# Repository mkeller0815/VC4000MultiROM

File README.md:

VC4000 MultiRom Modul
=====================

This is the approach to implement a MultiRom modul for the Interton VC4000.

![Overview] (https://github.com/mkeller0815/VC4000MultiROM/blob/master/doc/multirom_overview.jpg)

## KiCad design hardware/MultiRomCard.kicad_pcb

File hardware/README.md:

Hardware files for the MultiRom Cartridge
=========================================

You need [KiCad](http://kicad-pcb.org) 4.0 or later to open the project files.

The file MultiRomCard-cache.lib is included here for convenience. If you have
the KiCad standard symbol libraries installed, you do not need this file.
Currently, the only items from the standard libraries are the schematic symbols
for the 74HC595 Shift Register and the 74HC245 Bus Transciever. All other
schematic symbols are custom made and included in MultiRomCard.lib.

The Printouts folder contains PDF plots of the schematic and of the two current
PCB copper layers.  They can be used to create a double sided PCB with DIY
methods like toner transfer.

![Schematic] (https://rawgithub.com/mkeller0815/VC4000MultiROM/master/hardware/MultiRomCard.svg)

![PCB] (https://rawgithub.com/mkeller0815/VC4000MultiROM/master/hardware/MultiRomCard-brd.svg)

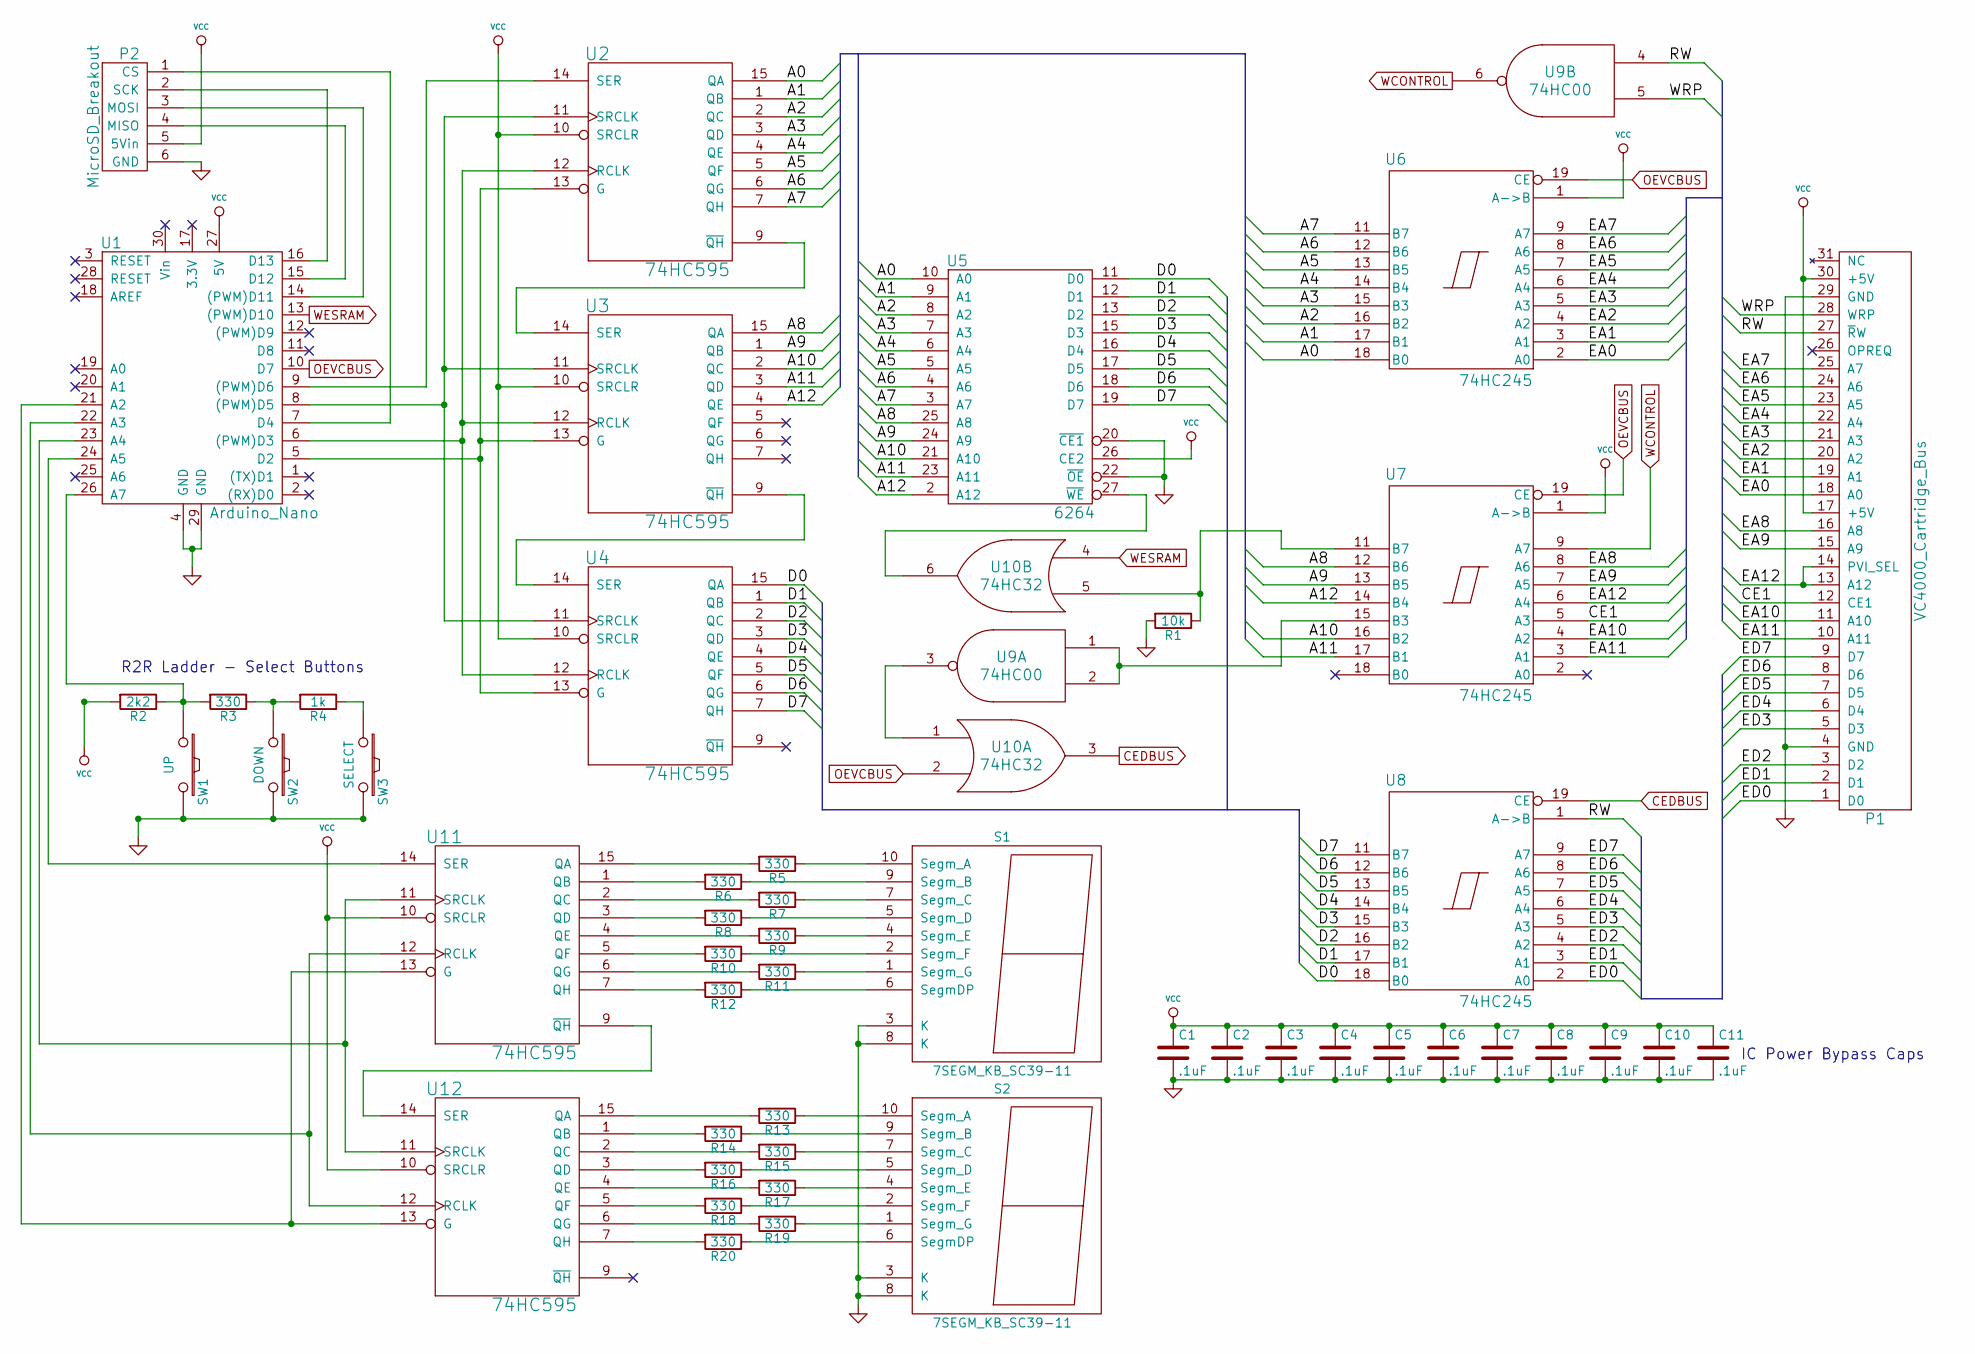
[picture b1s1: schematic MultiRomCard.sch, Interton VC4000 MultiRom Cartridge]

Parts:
C1, C2, C3, C4, C5, C6, C7, C8, C9, C10, C11: .1uF; C_Rect_L7_W2_P5_DIY
P1: VC4000_Cartridge_Bus; VC4000_CartridgeBus
P2: MicroSD_Breakout; Pin_Header_Straight_1x06
R1: 10k; Resistor_Horizontal_RM10mm
R2: 2k2; Resistor_Horizontal_RM10mm
R3, R5, R6, R7, R8, R9, R10, R11, R12, R13, R14, R15, R16, R17, R18, R19, R20: 330; Resistor_Horizontal_RM10mm
R4: 1k; Resistor_Horizontal_RM10mm
S1, S2: 7SEGM_KB_SC39-11; 7_Segment_Display_KB_13_10mm
SW1: UP; SW_PUSH_SMALL
SW2: DOWN; SW_PUSH_SMALL
SW3: SELECT; SW_PUSH_SMALL
U1: Arduino_Nano
U2, U3, U4, U11, U12: 74HC595; DIP-16_W7.62mm_LongPads
U5: 6264; DIP-28_W15.24mm_LongPads
U6, U7, U8: 74HC245; DIP-20_W7.62mm_LongPads
U9: 74HC00; DIP-14_W7.62mm_LongPads
U10: 74HC32; DIP-14_W7.62mm_LongPads

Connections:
/A0: U2.15 (QA), U5.10 (A0), U6.18 (B0)
/A1: U2.1 (QB), U5.9 (A1), U6.17 (B1)
/A2: U2.2 (QC), U5.8 (A2), U6.16 (B2)
/A3: U2.3 (QD), U5.7 (A3), U6.15 (B3)
/A4: U2.4 (QE), U5.6 (A4), U6.14 (B4)
/A5: U2.5 (QF), U5.5 (A5), U6.13 (B5)
/A6: U2.6 (QG), U5.4 (A6), U6.12 (B6)
/A7: U2.7 (QH), U5.3 (A7), U6.11 (B7)
/A8: U3.15 (QA), U5.25 (A8), U7.12 (B6)
/A9: U3.1 (QB), U5.24 (A9), U7.13 (B5)
/A10: U3.2 (QC), U5.21 (A10), U7.16 (B2)
/A11: U3.3 (QD), U5.23 (A11), U7.17 (B1)
/A12: U3.4 (QE), U5.2 (A12), U7.14 (B4)
/CE1: P1.12 (CE1), U7.5 (A3)
/D0: U4.15 (QA), U5.11 (D0), U8.18 (B0)
/D1: U4.1 (QB), U5.12 (D1), U8.17 (B1)
/D2: U4.2 (QC), U5.13 (D2), U8.16 (B2)
/D3: U4.3 (QD), U5.15 (D3), U8.15 (B3)
/D4: U4.4 (QE), U5.16 (D4), U8.14 (B4)
/D5: U4.5 (QF), U5.17 (D5), U8.13 (B5)
/D6: U4.6 (QG), U5.18 (D6), U8.12 (B6)
/D7: U4.7 (QH), U5.19 (D7), U8.11 (B7)
/EA0: P1.18 (A0), U6.2 (A0)
/EA1: P1.19 (A1), U6.3 (A1)
/EA2: P1.20 (A2), U6.4 (A2)
/EA3: P1.21 (A3), U6.5 (A3)
/EA4: P1.22 (A4), U6.6 (A4)
/EA5: P1.23 (A5), U6.7 (A5)
/EA6: P1.24 (A6), U6.8 (A6)
/EA7: P1.25 (A7), U6.9 (A7)
/EA8: P1.16 (A8), U7.8 (A6)
/EA9: P1.15 (A9), U7.7 (A5)
/EA10: P1.11 (A10), U7.4 (A2)
/EA11: P1.10 (A11), U7.3 (A1)
/EA12: P1.13 (A12), P1.14 (PVI_SEL), U7.6 (A4)
/ED0: P1.1 (D0), U8.2 (A0)
/ED1: P1.2 (D1), U8.3 (A1)
/ED2: P1.3 (D2), U8.4 (A2)
/ED3: P1.5 (D3), U8.5 (A3)
/ED4: P1.6 (D4), U8.6 (A4)
/ED5: P1.7 (D5), U8.7 (A5)
/ED6: P1.8 (D6), U8.8 (A6)
/ED7: P1.9 (D7), U8.9 (A7)
/RW: P1.27 (~R~W), U8.1 (A->B), U9.4
/WRP: P1.28 (WRP), U9.5
CEDBUS: U8.19 (CE), U10.3
GND: C1.2, C2.2, C3.2, C4.2, C5.2, C6.2, C7.2, C8.2, C9.2, C10.2, C11.2, P1.4 (GND), P1.29 (GND), P2.6 (GND), R1.2, S1.3 (K), S1.8 (K), S2.3 (K), S2.8 (K), SW1.2, SW2.2, SW3.2, U1.4 (GND), U1.29 (GND), U2.8 (GND), U3.8 (GND), U4.8 (GND), U5.14 (GND), U5.20 (~CE1), U5.22 (~OE), U6.10 (GND), U7.10 (GND), U8.10 (GND), U9.7 (GND), U10.7 (GND), U11.8 (GND), U12.8 (GND)
unnamed: P2.1 (CS), U1.7 (D4)
unnamed: P2.2 (SCK), U1.16 (D13)
unnamed: P2.3 (MOSI), U1.14 ((PWM)D11)
unnamed: P2.4 (MISO), U1.15 (D12)
unnamed: R1.1, U7.11 (B7), U10.5
unnamed: R2.1, R3.2, SW1.1, U1.26 (A7)
unnamed: R3.1, R4.2, SW2.1
unnamed: R4.1, SW3.1
unnamed: R5.1, S1.10 (Segm_A)
unnamed: R5.2, U11.15 (QA)
unnamed: R6.1, S1.9 (Segm_B)
unnamed: R6.2, U11.1 (QB)
unnamed: R7.1, S1.7 (Segm_C)
unnamed: R7.2, U11.2 (QC)
unnamed: R8.1, S1.5 (Segm_D)
unnamed: R8.2, U11.3 (QD)
unnamed: R9.1, S1.4 (Segm_E)
unnamed: R9.2, U11.4 (QE)
unnamed: R10.1, S1.2 (Segm_F)
unnamed: R10.2, U11.5 (QF)
unnamed: R11.1, S1.1 (Segm_G)
unnamed: R11.2, U11.6 (QG)
unnamed: R12.1, S1.6 (SegmDP)
unnamed: R12.2, U11.7 (QH)
unnamed: R13.1, S2.10 (Segm_A)
unnamed: R13.2, U12.15 (QA)
unnamed: R14.1, S2.9 (Segm_B)
unnamed: R14.2, U12.1 (QB)
unnamed: R15.1, S2.7 (Segm_C)
unnamed: R15.2, U12.2 (QC)
unnamed: R16.1, S2.5 (Segm_D)
unnamed: R16.2, U12.3 (QD)
unnamed: R17.1, S2.4 (Segm_E)
unnamed: R17.2, U12.4 (QE)
unnamed: R18.1, S2.2 (Segm_F)
unnamed: R18.2, U12.5 (QF)
unnamed: R19.1, S2.1 (Segm_G)
unnamed: R19.2, U12.6 (QG)
unnamed: R20.1, S2.6 (SegmDP)
unnamed: R20.2, U12.7 (QH)
unnamed: U1.5 (D2), U2.13 (G), U3.13 (G), U4.13 (G)
unnamed: U1.6 ((PWM)D3), U2.12 (RCLK), U3.12 (RCLK), U4.12 (RCLK)
unnamed: U1.8 ((PWM)D5), U2.11 (SRCLK), U3.11 (SRCLK), U4.11 (SRCLK)
unnamed: U1.9 ((PWM)D6), U2.14 (SER)
unnamed: U1.21 (A2), U11.13 (G), U12.13 (G)
unnamed: U1.22 (A3), U11.12 (RCLK), U12.12 (RCLK)
unnamed: U1.23 (A4), U11.11 (SRCLK), U12.11 (SRCLK)
unnamed: U1.24 (A5), U11.14 (SER)
unnamed: U2.9 (~QH), U3.14 (SER)
unnamed: U3.9 (~QH), U4.14 (SER)
unnamed: U7.15 (B3), U9.1, U9.2
unnamed: U9.3, U10.1
unnamed: U5.27 (~WE), U10.6
unnamed: U11.9 (~QH), U12.14 (SER)
OEVCBUS: U1.10 (D7), U6.19 (CE), U7.19 (CE), U10.2
VCC: C1.1, C2.1, C3.1, C4.1, C5.1, C6.1, C7.1, C8.1, C9.1, C10.1, C11.1, P1.17 (+5V), P1.30 (+5V), P2.5 (5Vin), R2.2, U1.27 (5V), U2.10 (SRCLR), U2.16 (VCC), U3.10 (SRCLR), U3.16 (VCC), U4.10 (SRCLR), U4.16 (VCC), U5.26 (CE2), U5.28 (VCC), U6.1 (A->B), U6.20 (VCC), U7.1 (A->B), U7.20 (VCC), U8.20 (VCC), U9.14 (VCC), U10.14 (VCC), U11.10 (SRCLR), U11.16 (VCC), U12.10 (SRCLR), U12.16 (VCC)
WCONTROL: U7.9 (A7), U9.6
WESRAM: U1.13 ((PWM)D10), U10.4

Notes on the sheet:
IC Power Bypass Caps
R2R Ladder - Select Buttons

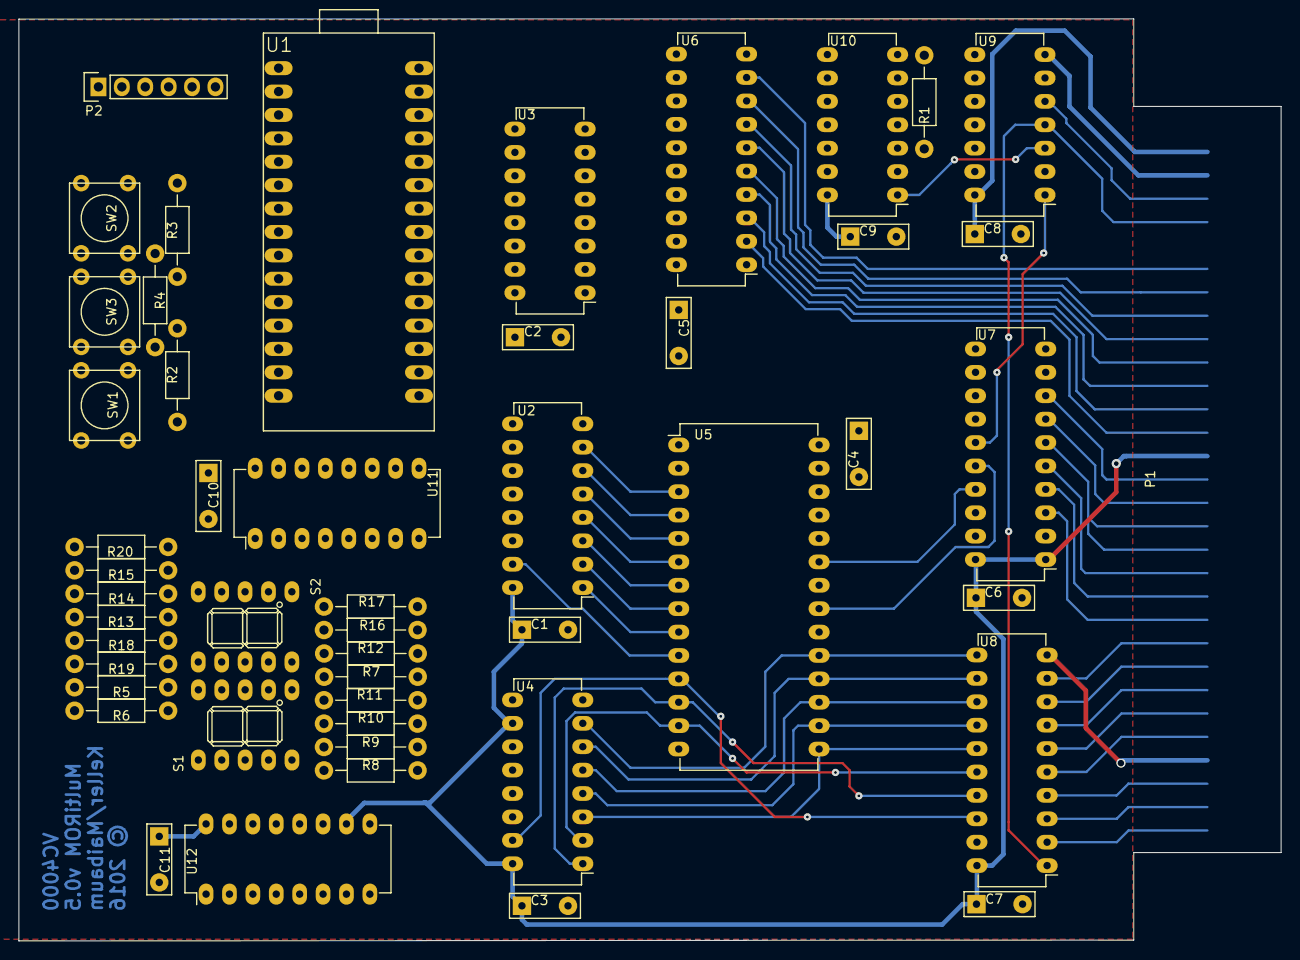
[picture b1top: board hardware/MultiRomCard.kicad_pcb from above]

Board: 2 copper layers, 137.0 x 100.1 mm, 50 parts (0 on the bottom side), 105 nets.

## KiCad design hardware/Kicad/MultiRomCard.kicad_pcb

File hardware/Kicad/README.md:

Kicad Project for the MultiRom Cartridge
========================================

You need a recent build of the Kicad “product” branch on Launchpad to open the
project. The current “stable” version will not work. Instructions on how to
install the Kicad “product” branch without compiling it yourself can be found
[on the official Kicad website]
(http://www.kicad-pcb.org/display/KICAD/Installing+KiCad) for GNU/Linux, Mac OSX
and Windows.

The MultiRomCard-cache.lib is included here for convenience. If you have the
Kicad standard symbol libraries installed, you do not need this file. Currently,
the only items from the standard libraries are the schematic symbols for the
74HC595 Shift Register and the 74HC245 Bus Transciever. All other schematic
symbols are custom made and included in MultiRomCard.lib.

![Schematic] (https://rawgithub.com/mkeller0815/flappy4000/master/MultiRom/hardware/Kicad/MultiRomCard.svg)

The current PCB is a first attempt to test the circuit in a more controlled
environment than on a breadboard (where it did not work!). So be warned, it is
*not* finished, yet!

![PCB] (https://rawgithub.com/mkeller0815/flappy4000/master/MultiRom/hardware/Kicad/MultiRomCard-brd.svg)

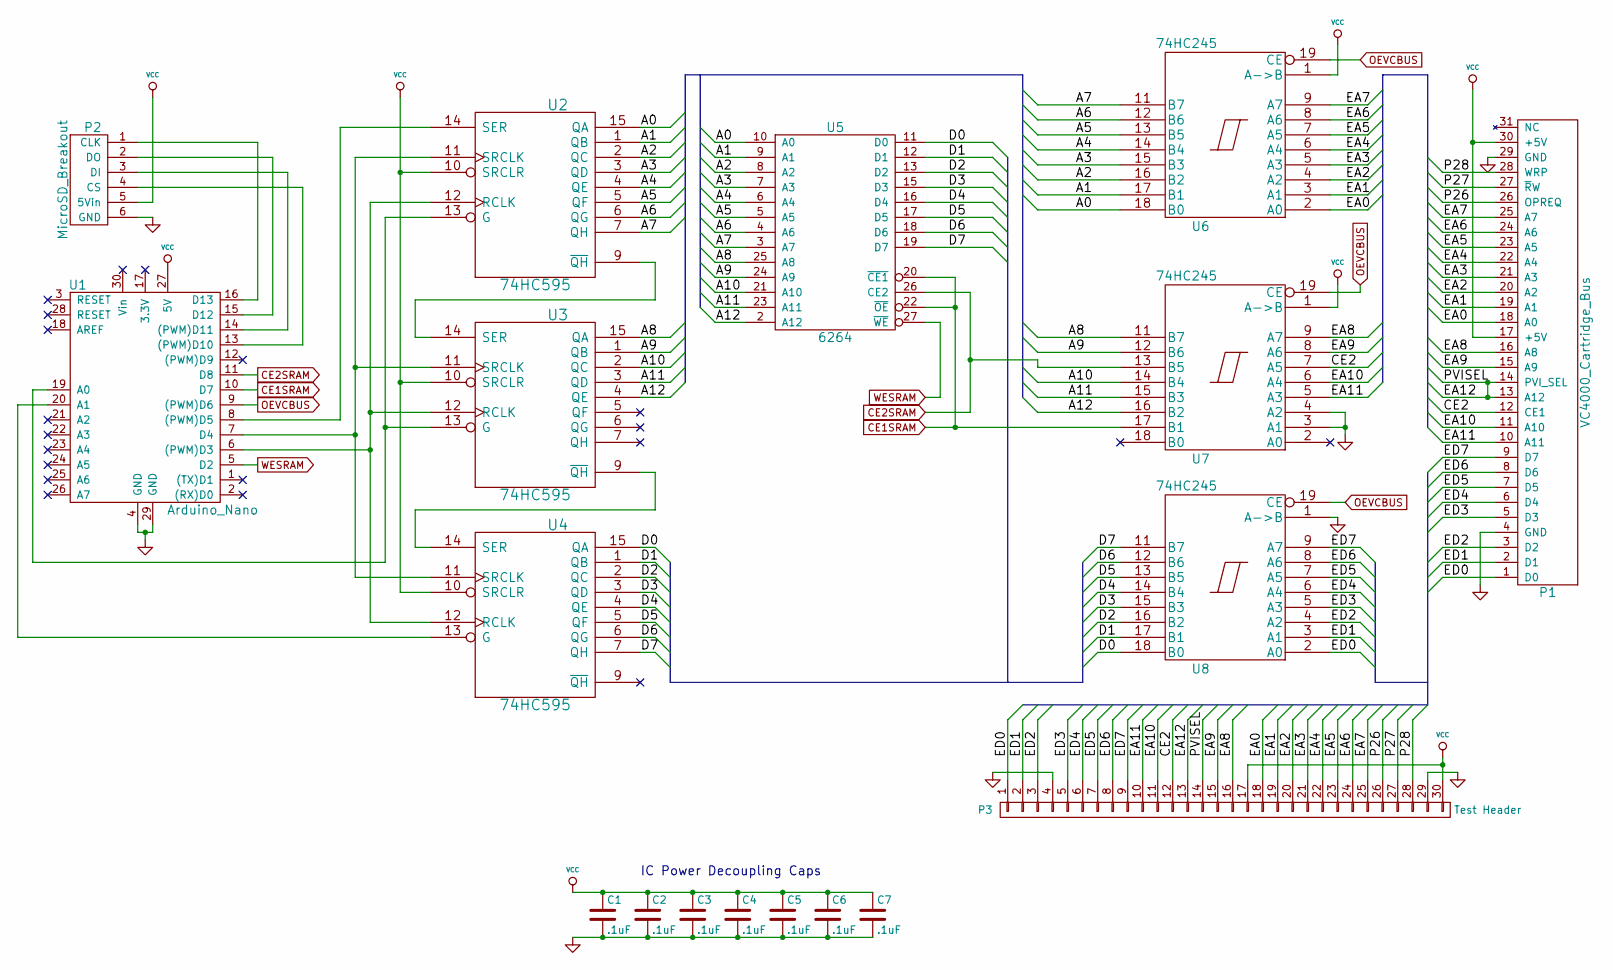
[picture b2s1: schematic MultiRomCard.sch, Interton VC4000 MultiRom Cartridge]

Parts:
C1, C2, C3, C4, C5, C6, C7: .1uF; C_Disc_D6_P5
P1: VC4000_Cartridge_Bus; VC4000_CartridgeBus
P2: MicroSD_Breakout; Pin_Header_Straight_1x06
P3: Test Header; Pin_Header_Straight_1x30
U1: Arduino_Nano
U2, U3, U4: 74HC595; DIP-16__300_ELL
U5: 6264; DIP-28__600_ELL
U6, U7, U8: 74HC245; DIP-20__300_ELL

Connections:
/A0: U2.15 (QA), U5.10 (A0), U6.18 (B0)
/A1: U2.1 (QB), U5.9 (A1), U6.17 (B1)
/A2: U2.2 (QC), U5.8 (A2), U6.16 (B2)
/A3: U2.3 (QD), U5.7 (A3), U6.15 (B3)
/A4: U2.4 (QE), U5.6 (A4), U6.14 (B4)
/A5: U2.5 (QF), U5.5 (A5), U6.13 (B5)
/A6: U2.6 (QG), U5.4 (A6), U6.12 (B6)
/A7: U2.7 (QH), U5.3 (A7), U6.11 (B7)
/A8: U3.15 (QA), U5.25 (A8), U7.11 (B7)
/A9: U3.1 (QB), U5.24 (A9), U7.12 (B6)
/A10: U3.2 (QC), U5.21 (A10), U7.14 (B4)
/A11: U3.3 (QD), U5.23 (A11), U7.15 (B3)
/A12: U3.4 (QE), U5.2 (A12), U7.16 (B2)
/CE2: P1.12 (CE1), P3.12, U7.7 (A5)
/D0: U4.15 (QA), U5.11 (D0), U8.18 (B0)
/D1: U4.1 (QB), U5.12 (D1), U8.17 (B1)
/D2: U4.2 (QC), U5.13 (D2), U8.16 (B2)
/D3: U4.3 (QD), U5.15 (D3), U8.15 (B3)
/D4: U4.4 (QE), U5.16 (D4), U8.14 (B4)
/D5: U4.5 (QF), U5.17 (D5), U8.13 (B5)
/D6: U4.6 (QG), U5.18 (D6), U8.12 (B6)
/D7: U4.7 (QH), U5.19 (D7), U8.11 (B7)
/EA0: P1.18 (A0), P3.18, U6.2 (A0)
/EA1: P1.19 (A1), P3.19, U6.3 (A1)
/EA2: P1.20 (A2), P3.20, U6.4 (A2)
/EA3: P1.21 (A3), P3.21, U6.5 (A3)
/EA4: P1.22 (A4), P3.22, U6.6 (A4)
/EA5: P1.23 (A5), P3.23, U6.7 (A5)
/EA6: P1.24 (A6), P3.24, U6.8 (A6)
/EA7: P1.25 (A7), P3.25, U6.9 (A7)
/EA8: P1.16 (A8), P3.16, U7.9 (A7)
/EA9: P1.15 (A9), P3.15, U7.8 (A6)
/EA10: P1.11 (A10), P3.11, U7.6 (A4)
/EA11: P1.10 (A11), P3.10, U7.5 (A3)
/EA12: P1.13 (A12), P1.14 (PVI_SEL), P3.13, P3.14
/ED0: P1.1 (D0), P3.1, U8.2 (A0)
/ED1: P1.2 (D1), P3.2, U8.3 (A1)
/ED2: P1.3 (D2), P3.3, U8.4 (A2)
/ED3: P1.5 (D3), P3.5, U8.5 (A3)
/ED4: P1.6 (D4), P3.6, U8.6 (A4)
/ED5: P1.7 (D5), P3.7, U8.7 (A5)
/ED6: P1.8 (D6), P3.8, U8.8 (A6)
/ED7: P1.9 (D7), P3.9, U8.9 (A7)
/P26: P1.26 (OPREQ), P3.26
/P27: P1.27 (~R~W), P3.27
/P28: P1.28 (WRP), P3.28
CE1SRAM: U1.10 (D7), U5.20 (~CE1), U5.22 (~OE), U7.17 (B1)
CE2SRAM: U1.11 (D8), U5.26 (CE2), U7.13 (B5)
GND: C1.2, C2.2, C3.2, C4.2, C5.2, C6.2, C7.2, P1.4 (GND), P1.29 (GND), P2.6 (GND), P3.4, P3.29, U1.4 (GND), U1.29 (GND), U2.8 (GND), U3.8 (GND), U4.8 (GND), U5.14 (GND), U6.10 (GND), U7.3 (A1), U7.4 (A2), U7.10 (GND), U8.1 (A->B), U8.10 (GND)
unnamed: P2.1 (CLK), U1.16 (D13)
unnamed: P2.2 (DO), U1.15 (D12)
unnamed: P2.3 (DI), U1.14 ((PWM)D11)
unnamed: P2.4 (CS), U1.13 ((PWM)D10)
unnamed: U1.6 ((PWM)D3), U2.12 (RCLK), U3.12 (RCLK), U4.12 (RCLK)
unnamed: U1.7 (D4), U2.11 (SRCLK), U3.11 (SRCLK), U4.11 (SRCLK)
unnamed: U1.8 ((PWM)D5), U2.14 (SER)
unnamed: U1.19 (A0), U2.13 (G), U3.13 (G)
unnamed: U1.20 (A1), U4.13 (G)
unnamed: U2.9 (~QH), U3.14 (SER)
unnamed: U3.9 (~QH), U4.14 (SER)
OEVCBUS: U1.9 ((PWM)D6), U6.19 (CE), U7.19 (CE), U8.19 (CE)
VCC: C1.1, C2.1, C3.1, C4.1, C5.1, C6.1, C7.1, P1.17 (+5V), P1.30 (+5V), P2.5 (5Vin), P3.17, P3.30, U1.27 (5V), U2.10 (SRCLR), U2.16 (VCC), U3.10 (SRCLR), U3.16 (VCC), U4.10 (SRCLR), U4.16 (VCC), U5.28 (VCC), U6.1 (A->B), U6.20 (VCC), U7.1 (A->B), U7.20 (VCC), U8.20 (VCC)
WESRAM: U1.5 (D2), U5.27 (~WE)

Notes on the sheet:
IC Power Decoupling Caps

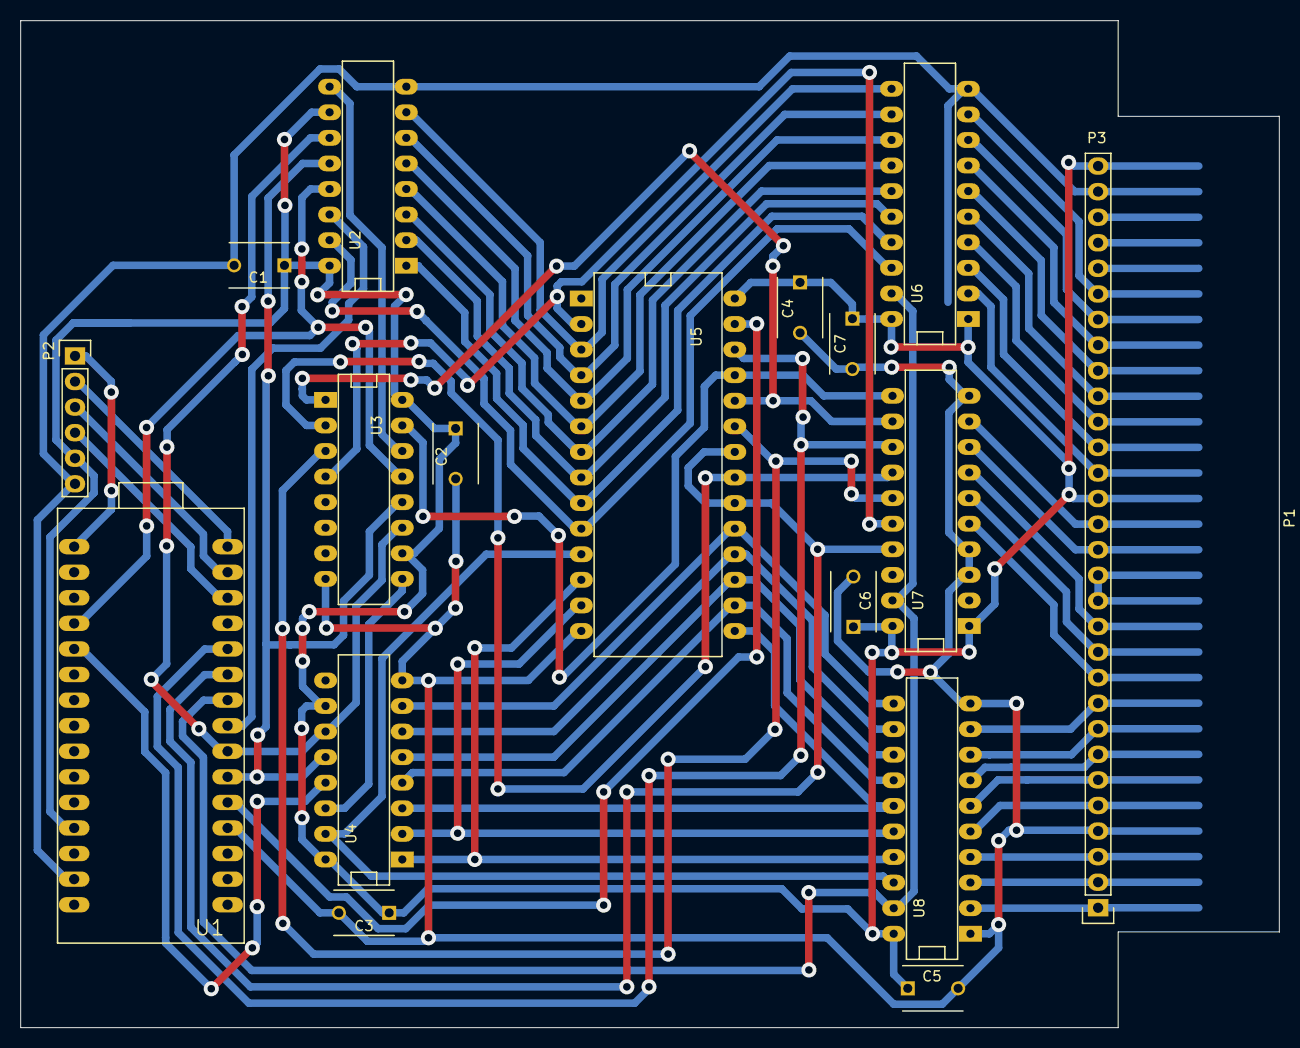
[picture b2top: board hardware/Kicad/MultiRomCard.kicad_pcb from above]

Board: 2 copper layers, 125.0 x 100.0 mm, 18 parts (0 on the bottom side), 63 nets.

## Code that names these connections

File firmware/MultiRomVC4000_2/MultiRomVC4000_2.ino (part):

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#define OEDATA    A1  // _G DATA BUS
#define OEADDRESS A0  // _G ADDRESS BUS

#define OEVCBUS   6

#define CE1SRAM   7
#define CE2SRAM   8

#define LED       13

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  pinMode(WR, OUTPUT);
  pinMode(OEDATA, OUTPUT);
  pinMode(OEADDRESS, OUTPUT);
  pinMode(OEVCBUS, OUTPUT);
  pinMode(LED, OUTPUT);

  disableVCBus();
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}

void enableSRAM() {
  pinMode(CE1SRAM, OUTPUT);
  pinMode(CE2SRAM, OUTPUT);
  digitalWrite(CE1SRAM, LOW);
  digitalWrite(CE2SRAM, HIGH);
}
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  // bad idea!).
  digitalWrite(CE1SRAM, LOW);
  digitalWrite(CE2SRAM, LOW);
  pinMode(CE1SRAM, INPUT);
  pinMode(CE2SRAM, INPUT);
}

void disableVCBus() {
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
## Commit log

2014-11-28 added MultiRom project added first code parts
2014-11-28 dded some comments to the current firmware code
2014-11-28 added MultiRom picture to readme
2014-11-28 added doc
2014-11-28 bug in README
2014-11-28 added new files
2015-02-03 Added helper script to convert roms into c source headers.
2015-02-03 A little more documentation in the script.
2015-02-04 added new MultiROM Arduino Firmware
2015-02-05 added pinout document for ROM slot new test firmware version
2015-02-11 Add initial Kicad project files.
2015-02-11 Add README for the Kicad project directory.
2015-02-11 Hopefully correct the link to the schematic SVG.
2015-02-12 Add Kicad specific .gitignore.
2015-02-17 Correct schematic error: DIR pin logic swap on bus transcievers.
2015-02-17 Schematic: Remove left-over junction.
2015-02-17 Update README in hardware folder.
2015-02-25 Small cosmetic changes in schematic
    - Account for changes in Kicad symbol libraries that affected power
    symbols GND and VCC.
2015-02-25 added new test sketch for 74hc245 testing on arduino mega
2015-02-28 Make most pin properties of VC4000_Cartridge_Bus passive to silence Eeschema DRC.
2015-03-07 Schematic: Change size of global labels.
2015-03-19 updated SRAM /CE1 & CE2 connection to Arduino and bus transceiver
2015-03-19 Altered PROGMEM usage due to AVR libc changes.
2015-03-19 Add tiny delay in SRAM_readout.ino
2015-03-20 Updated date string in Schematic.
2015-04-23 Preparations for PCB layout
    - Created footprints for Cartridge Bus and Arduino UNO,
    - Modified Arduino UNO schematic symbol to include pin numbers,
    - Created initial netlist, and
    - Spread all footprints on board, no traces yet.
2015-04-26 Cartridge bus footprint: Move net connections towards the edges.
2015-04-26 Euro PCB outline and some part changes (BREAKS CURRENT FIRMWARE!)
    - Swapped A and B sides on Bus transcievers for easier tracing.
    (Not sure if this is ideal, yet, but certainly better than
    before!). THIS BREAKS CURRENT FIRMWARE! Need to change
    direction bits!
    - Prefix bus labels from the cartridge to the transcievers with 'E'
    (for 'external') to de-confuse Pcbnew.
2015-04-26 Update SVG and PDF.
2015-05-06 Move "CE2" track to another BT pin and remove special.lib.
2015-05-06 Updated SVG schematic.
2015-05-06 Move footprints a little.
2015-05-06 First attempt at routing.
2015-05-21 [PCB] First version with all nets connected.
2015-05-21 Ignore Pcbnew’s auto-backups.
2015-05-21 [PCB] True first version with all nets connected.
2015-05-21 Added SVG of PCB, updated README accordingly.
2015-05-21 Corrected link to Kicad install instructions in README.
2015-05-26 [PCB] Add ground copper zone; minor reroutings.
2015-06-20 [PCB] Make Cartridge Bus Pins 1mm longer.
2015-06-20 [SCH] Corrected an error with the internal address bus.
2015-06-20 [SCH/PCB] Added IC power decoupling caps.
2015-06-20 Remove .cmp file as it is no longer needed.
    (Recent changes in Kicad made this file obsolete.)
2015-06-20 [PCB] Added missing last connection.
2015-06-20 [PCB] Corrected DRC error (track near pad).
2015-06-20 [PCB] Corrected typo in board credits.
2015-06-20 [SCH/PCB] Match credits in both Schematic and PCB.
2015-06-21 [SCH/PCB] Added and connected missing Arduino GND Pins.
2015-06-22 [SCH/PCB] Cleaning up both schematic and PCB a bit.
2015-06-22 [SCH/PCB] Add Pin header for MicroSD Card Breakout Board.
2015-06-22 [PCB] Slightly bigger drill holes for Arduino footprint.
2015-06-22 [SCHSYM] Add footprint filter to current custom schematic symbols.
2015-06-22 [SCH/PCB] Replace Arduino UNO by Arduino Nano
    - TODO: Shrink board outlines to account for smaller Arduino board.
2015-06-23 [PCB] Some minor routing improvements.
2015-06-25 [PCB] Increase one inner GND zone a little.
2015-06-25 [PCB] Shrink PCB to fit closer to the now used Arduino Nano.
2015-06-25 [SCH/PCB] Add pin header for testing purposes.
2015-06-29 [PCB] Change GND copper zone a bit.
2015-06-29 [SCH symbols] Correct some pins for ERC.
2015-06-29 [SCH/PCB] Correct 74HC245 direction pins.
2015-06-29 Added printouts.
2015-06-29 [PCB] Corrected printout (was not mirrored).
2015-07-20 [PCB] Added USB connector overhang to Arduino Nano footprint.
2015-07-21 [SCH/PCB] Corrected wrong analog pin numbering in Arduino Nano symbol.
2015-07-21 [FW] Several changes to account for prototype PCB
    - Swap 595 OE pins for data and address bus
    - Fixed off-by-one error in SRAM copy code
    - Fixed occasional bug with CE1/CE2 pins on Arduino
    which could stay at +5V if they were HIGH before
    switching them to INPUT (high-Z) mode.
    - Move status LED blinking code into loop()
2015-07-21 [FW] Some more code cleanup.
2015-07-21 Clean up firmware folder.
    - The current firmware is called MultiRomVC4000.ino
    - Old code and test tools have been moved to old/
2015-07-21 Move old hardware layout out of the way.
2015-07-21 Move contents of Kicad folder to root hardware folder.
2015-07-21 Correct links to SVGs in hardware/README.md
2015-07-22 Update the bin2c.py helper script.
2015-07-22 [FW] Remove double call to enableSRAM().
2015-07-22 [SCH/PCB] A12+PVI_SEL needs to be connected to /CE1.
2015-07-22 [SCH] Minimal cosmetic changes.
2015-07-23 added ROM readout test sketch
2015-07-27 [FW] Load ROM file from SD card via simple 'config.txt' interface.
2015-07-27 [DOC] Added ROM status file (README.md in doc/).
2015-07-27 [DOC] Added links to last tested commits.
2015-07-27 Another test with commit links.
2015-07-27 Test if it works outside tables.
2015-07-27 Only the full SHA-1 on a line?
2015-07-27 [DOC] revert commit ref to shortened SHA-1 per line.
    Does not work (gets not converted to links), but I have no idea, why...
2015-07-27 [DOC] Tested all 2K roms.
2015-07-28 [DOC] Add statistics.
2015-07-28 [DOC] Small cleanup.
2015-07-28 [SCH/PCB] Rotate MicroSD breakout header.
2015-07-30 added read/write control and 6k ROM size
2015-07-31 [FW] Code cleanup and documentation.
2015-08-02 [FW] Some changes to allow RAM access.
2015-08-03 [HW/FW] Incorporate latest changes into hardware and firmware.
    - From now on, we should call the hardware rev. 0.2.
    - All games should now work (ROM and ROM+RAM)
    - Up to 6K (5.5K) ROM is currently allowed (7.5K should be
    possible, too, with one line change in the FW.)
2015-08-04 version string added on copper side
2015-08-04 [HW] A little cleanup on the schematic, new PDF printouts.
2015-08-16 added 3 push buttons and a display prot connected to I2C
2015-08-16 increased size of several vias for better soldering
2015-08-19 [HW] PCB cleanup and new printouts.
2015-08-19 clean up of schema for additional components
2015-08-19 added 2x 7-segment displays and shift register for display
2015-08-21 [FW] Missing firmware changes for v. 0.2.
2015-08-23 [PCB] Some last optimizations for v. 0.2.
2015-08-24 [HW] Update PCB to v. 0.3 (include 7-segm display).
2015-08-24 [DOC] Updated ROM status table.
2015-08-30 [PCB] New cap footprint with larger pads...
    - ... should allow for easier hand soldering.
    - Some minor reroutings to decrease copper loss when etching the board.
2015-09-01 added ground plane on front side
2015-09-15 [FW] Cleanup
    - Tidying up the #defines and globals.
    - Removing last remains of obsolete enableSRAM().
2015-09-16 adding Test sketches
2015-09-16 added I2C library
2015-09-17 [FW] Allow user selection of ROM file on-board.
2015-09-17 [FW] Properly init 7-segment display.
2015-09-17 [FW] Some improvements
    - Faster ROM loading
    - Leading zeroes for ROM number
2015-09-22 7 segment test
2015-09-22 7 segment test2
2015-09-22 7 segment display function in test sketch
2015-09-22 firmware adjusted for new 7-segment display
2015-09-23 [FW] Status indication now on 7-segment display.
2015-09-23 flyer added
2015-09-23 flyer typo corrected
2015-09-24 [FW] Some cleanup, some more comments.
2015-09-29 Cleanup in hardware folder:
    - Delete and ignore PCBNew's autosave files.
    - Delete duplicated PDF file of PCB layout (they belong into Printouts/)
2015-09-29 Renamed scripts/ to utilities/
2015-09-29 Add ROMdumper utility (Arduino Mega based).
2015-09-30 [FW] Re-introduce write delay
    Otherwise game #9 (Intelligenz I / Labyrinth) does not load correctly.
2015-09-30 [FW] Use delayMicroseconds() for write delay.
    Delay of 10us is intentional, since the function is only guaranteed
    to work reliably with 3us and larger values, so we better stay safe.
    A delay of 20us is still faster than the millisecond delay()!
2015-09-30 [FW] Allow for (future?) games with up to 8K of ROM/RAM.
2016-03-28 [PCB] Changes for v0.4
    - Arduino USB port to the border of the mainboard
    - Controls to the top
    - Add PDF printout of front copper layer
2016-03-28 [SCH] Update for v0.4
2016-03-28 Updated README in hardware folder.
2016-03-28 Removed ancient DipTrace layout file.
2016-04-07 moved repository
2016-04-07 path adjusted
2016-04-08 Corrected image links to SCH and PCB in hardware/README.md
2016-04-26 corrected soldermask layer for connector foodprint
2016-04-27 Correct soldermask layer for all copper stripes in Cartridge Bus Footprint (in library).
2016-08-24 V0.4 soldered, pictures added
2016-09-02 added new flyer for CC2016
2016-09-05 github pages added
2016-09-05 .gitmodules
2016-09-15 Updated copyright in LICENSE.
2016-09-15 Corrected typo in README.md.
2017-03-03 new pcb version

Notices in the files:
hardware/MultiRomCard.kicad_pcb:
© 2016
